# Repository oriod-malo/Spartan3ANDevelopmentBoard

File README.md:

# Spartan-3AN Development Board

## Description

A custom development board built over a Spartan-3AN FPGA. <br>
Built over 4 layers, it gives controlability over the Spartan-3AN Mode Pins through switches. This way it can be programmed both via JTAG and USB.
For the different combinations of Mode switches refer to Spartan-3AN documentation. For Slave Mode (where PIC32M250F128D acts as master), all three mode pins have to be HIGH.<br>
Note that the PIC32M250F128D requires adequate programming to function as the Master for the FPGA. 

## Features
* Spartan 3AN XC3S50AN-TQG144 FPGA
* PIC32MX250F128D-IPT for connecting with USB
* JTAG Header Pins
* M0-2 switches in order to switch from JTAG to Slave Mode to other modes and viceversa
* 4 Custom Switches
* 4 Pushbuttons
* 4 LED Lights
* VGA Connections
* All other pins connected with headers or sockets

## Images

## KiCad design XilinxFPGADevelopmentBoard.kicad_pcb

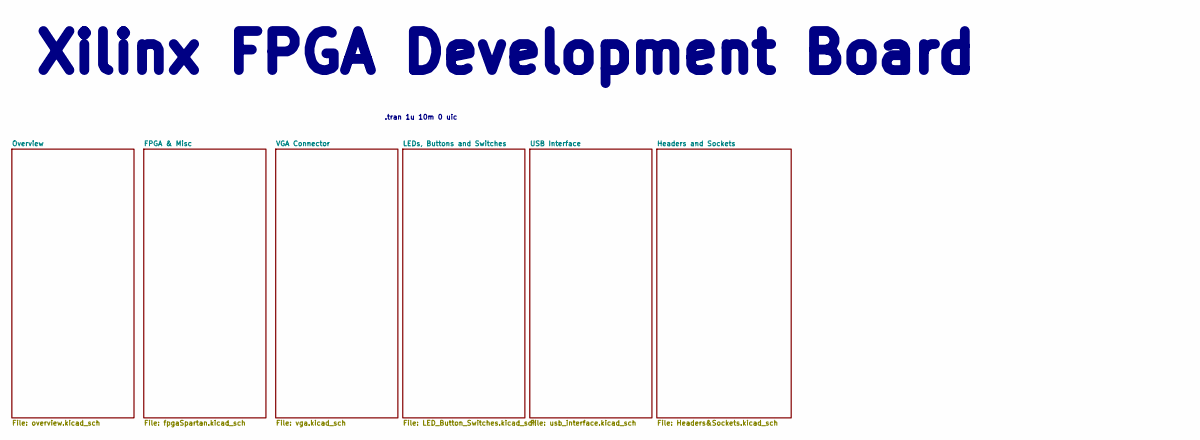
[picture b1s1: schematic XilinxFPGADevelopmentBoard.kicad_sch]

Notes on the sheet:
.tran 1u 10m 0 uic
Xilinx FPGA Development Board

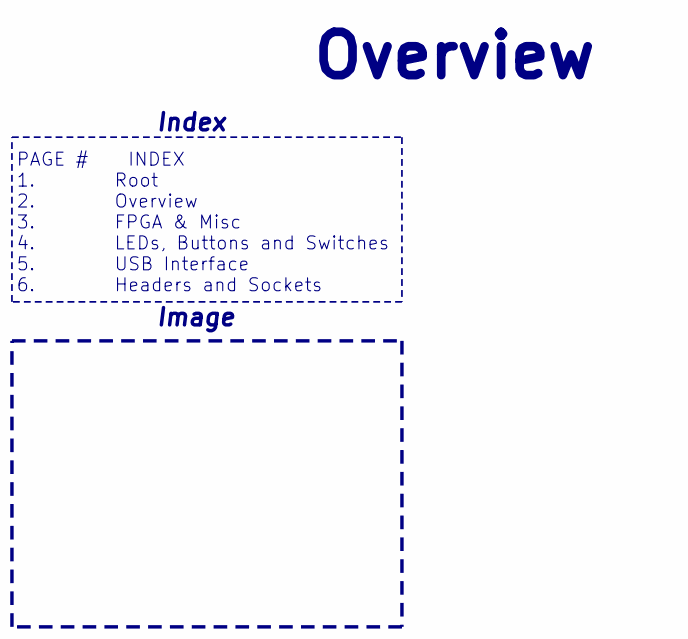
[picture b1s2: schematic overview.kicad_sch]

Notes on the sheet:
Image
Index
PAGE # INDEX 1. Root 2. Overview 3. FPGA & Misc 4. LEDs, Buttons and Switches 5. USB Interface 6. Headers and Sockets
Overview

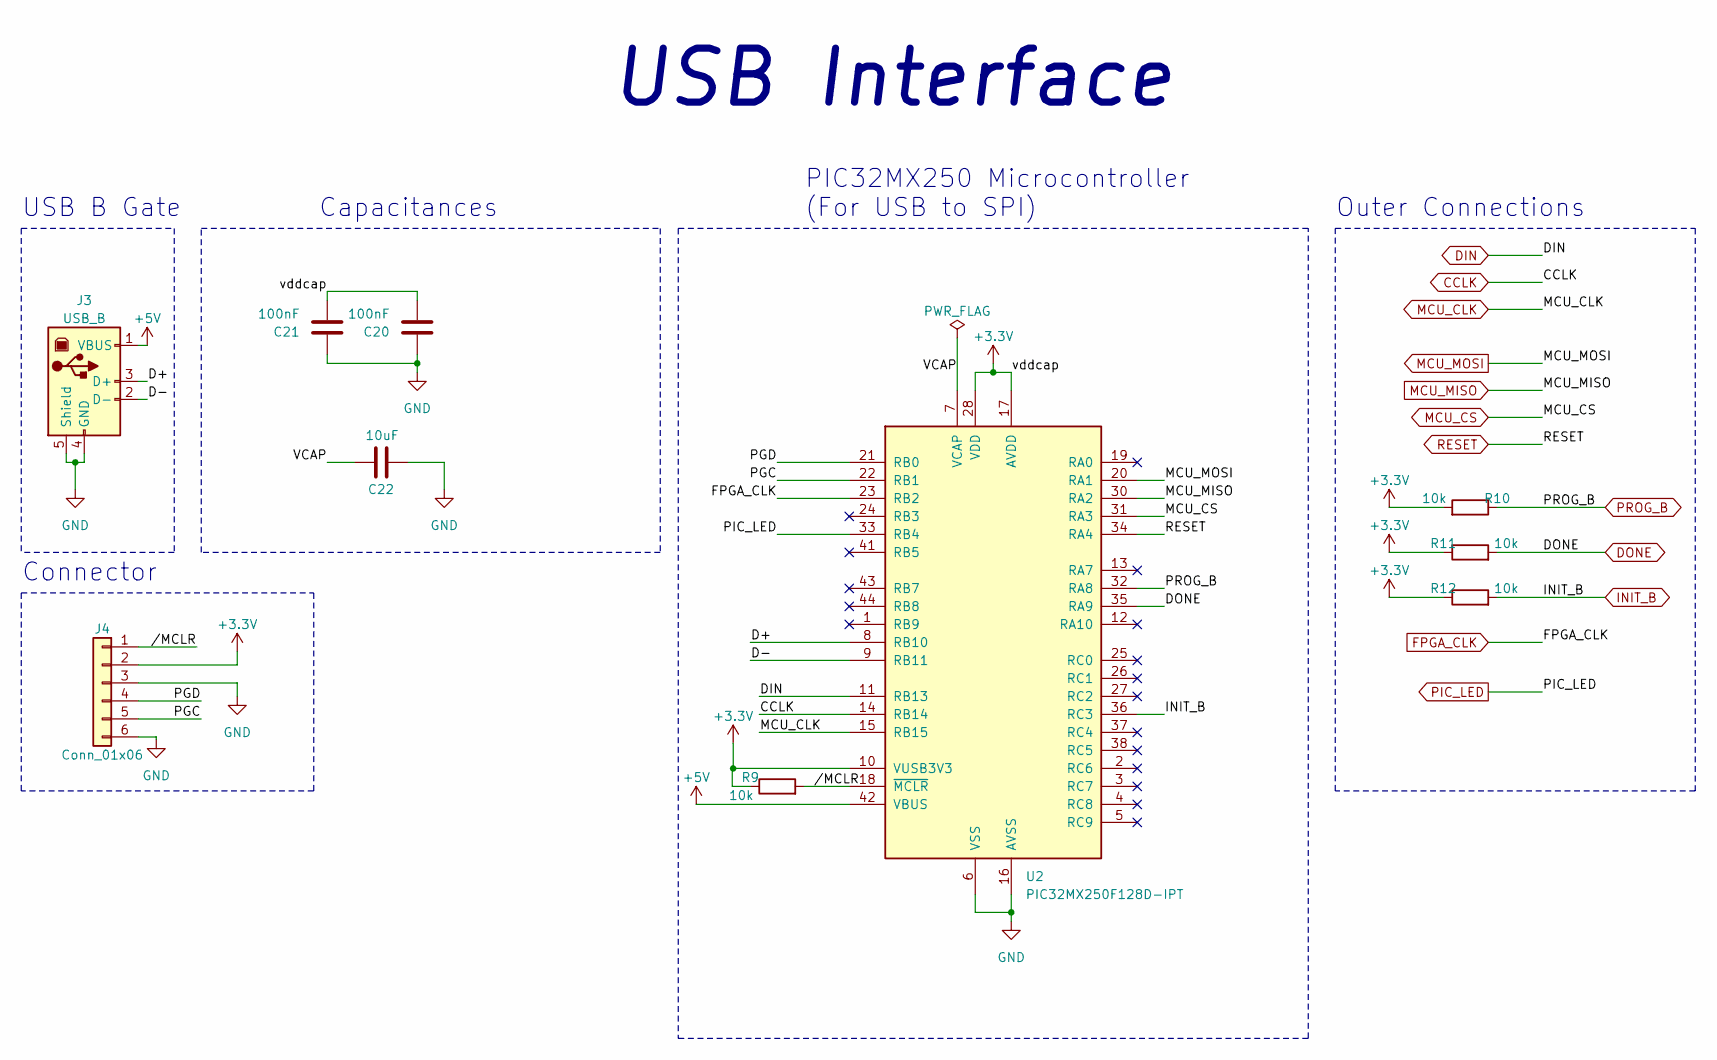
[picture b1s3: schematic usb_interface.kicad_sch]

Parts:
C20, C21: 100nF; C_0201_0603Metric
C22: 10uF; C_0201_0603Metric
J3: USB_B; USB_B_Lumberg_2411_02_Horizontal
J4: Conn_01x06; PinHeader_1x06_P2.54mm_Vertical
R9, R10, R11, R12: 10k; R_0201_0603Metric
U2: PIC32MX250F128D-IPT; TQFP-44_10x10mm_P0.8mm

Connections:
+3.3V: C20.2, C21.2, J4.2, R9.1, R10.2, R11.1, R12.1, U2.10 (VUSB3V3), U2.17 (AVDD), U2.28 (VDD), U2.40 (VDD); also elsewhere on the board
+5V: J3.1 (VBUS), U2.42 (VBUS)
/USB Interface/D+: J3.3 (D+), U2.8 (RB10)
/USB Interface/D-: J3.2 (D-), U2.9 (RB11)
/USB Interface/PGC: J4.5, U2.22 (RB1)
/USB Interface/PGD: J4.4, U2.21 (RB0)
/USB Interface/VCAP: C22.1, U2.7 (VCAP)
/USB Interface//MCLR: J4.1, R9.2, U2.18 (~MCLR)
CCLK: U2.14 (RB14); also elsewhere on the board
DIN: U2.11 (RB13); also elsewhere on the board
DONE: R11.2, U2.35 (RA9); also elsewhere on the board
FPGA_CLK: U2.23 (RB2); also elsewhere on the board
GND: C20.1, C21.1, C22.2, J3.4 (GND), J3.5 (Shield), J4.3, J4.6, U2.6 (VSS), U2.16 (AVSS), U2.29 (VSS), U2.39 (VSS); also elsewhere on the board
INIT_B: R12.2, U2.36 (RC3); also elsewhere on the board
MCU_CLK: U2.15 (RB15); also elsewhere on the board
MCU_CS: U2.31 (RA3); also elsewhere on the board
MCU_MISO: U2.30 (RA2); also elsewhere on the board
MCU_MOSI: U2.20 (RA1); also elsewhere on the board
PIC_LED: U2.33 (RB4); also elsewhere on the board
PROG_B: R10.1, U2.32 (RA8); also elsewhere on the board
RESET: U2.34 (RA4); also elsewhere on the board

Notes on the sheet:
Capacitances
USB Interface
Outer Connections
USB B Gate
PIC32MX250 Microcontroller (For USB to SPI)
Connector

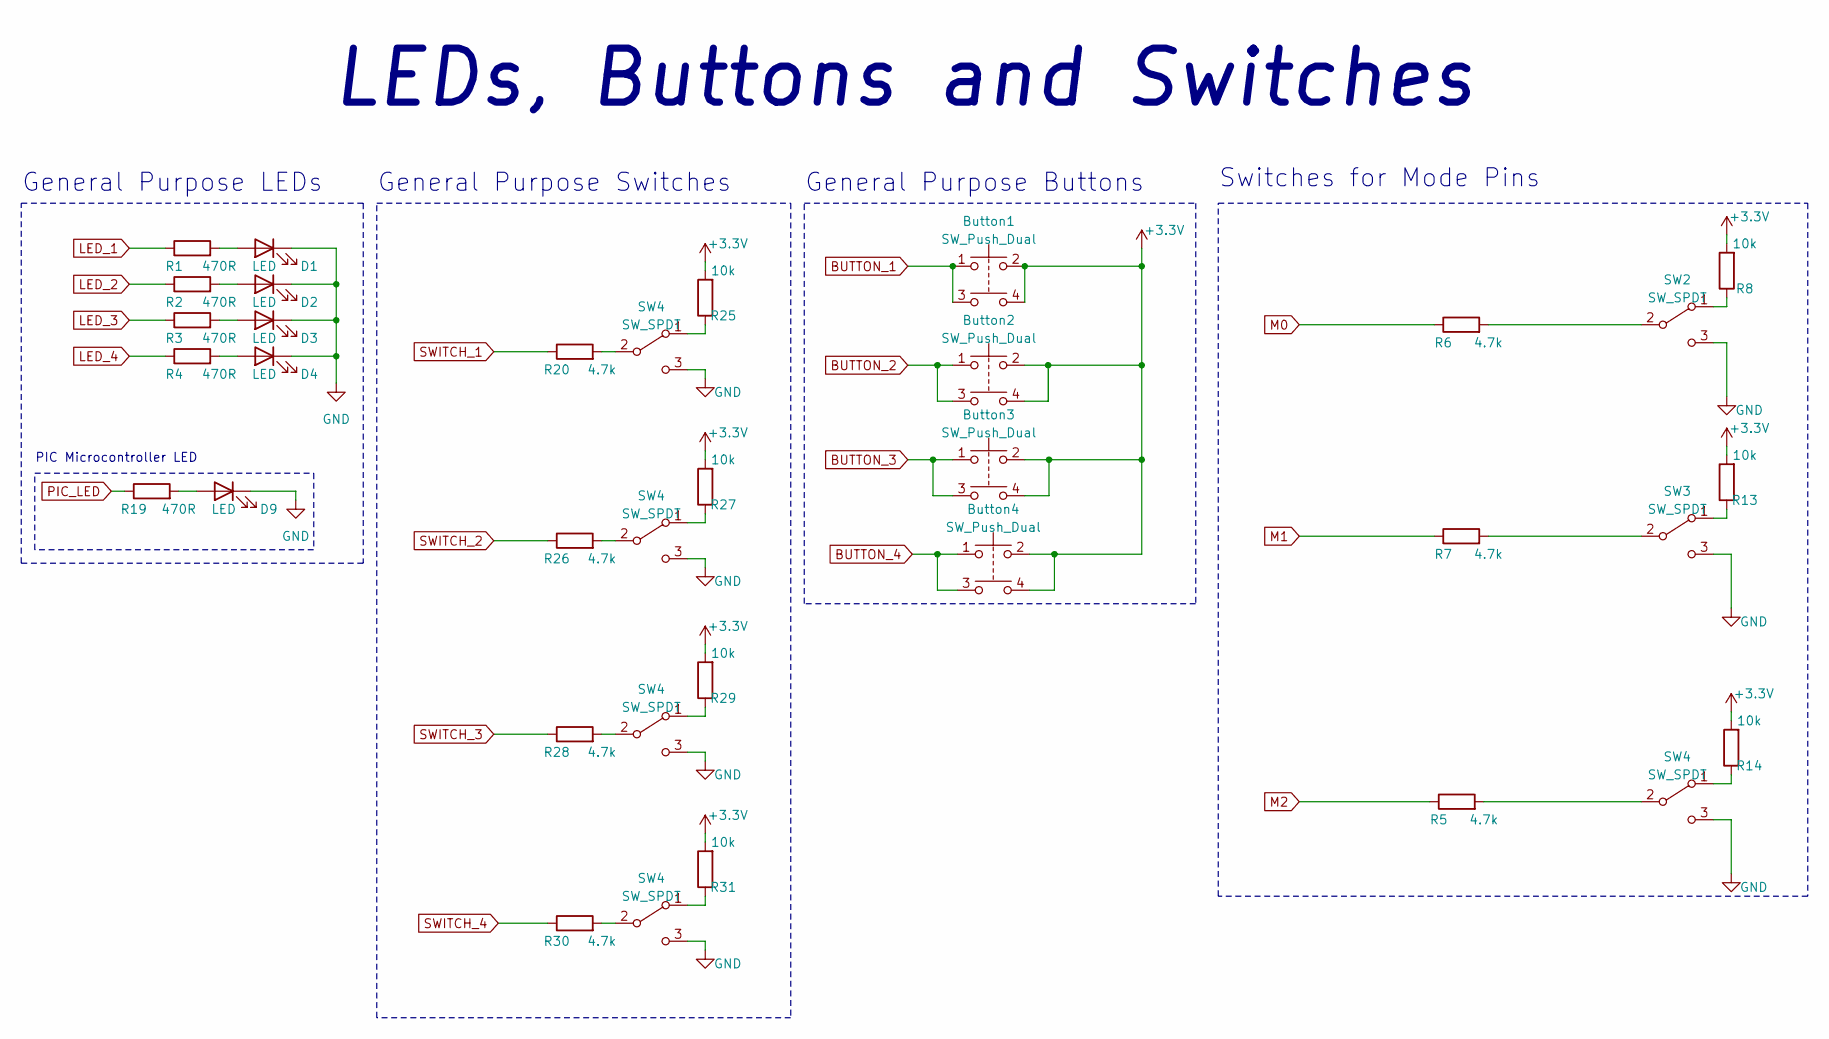
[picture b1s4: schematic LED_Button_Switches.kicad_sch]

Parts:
Button1, Button2, Button3, Button4: SW_Push_Dual; SW_PUSH_6mm
D1, D2, D3, D4: LED; LED_1206_3216Metric
D9: LED; LED_0201_0603Metric
R1, R2, R3, R4: 470R; R_1206_3216Metric
R5, R6, R7, R20, R26, R28, R30: 4.7k; R_0201_0603Metric
R8, R13, R14, R25, R27, R29, R31: 10k; R_0201_0603Metric
R19: 470R; R_0201_0603Metric
SW2, SW3, SW4: SW_SPDT; SW_500SSP1S2M2QEA

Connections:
+3.3V: Button1.2, Button1.4, Button2.2, Button2.4, Button3.2, Button3.4, Button4.2, Button4.4, R8.2, R13.2, R14.2, R25.2, R27.2, R29.2, R31.2; also elsewhere on the board
BUTTON_1: Button1.1, Button1.3; also elsewhere on the board
BUTTON_2: Button2.1, Button2.3; also elsewhere on the board
BUTTON_3: Button3.1, Button3.3; also elsewhere on the board
BUTTON_4: Button4.1, Button4.3; also elsewhere on the board
GND: D1.1 (K), D2.1 (K), D3.1 (K), D4.1 (K), D9.1 (K), SW2.3 (C), SW3.3 (C); also elsewhere on the board
LED_1: R1.1; also elsewhere on the board
LED_2: R2.1; also elsewhere on the board
LED_3: R3.1; also elsewhere on the board
LED_4: R4.1; also elsewhere on the board
M0: R6.1; also elsewhere on the board
M1: R7.1; also elsewhere on the board
M2: R5.1; also elsewhere on the board
unnamed: D1.2 (A), R1.2
unnamed: D2.2 (A), R2.2
unnamed: D3.2 (A), R3.2
unnamed: D4.2 (A), R4.2
unnamed: D9.2 (A), R19.2
unnamed 63: R25.1; also elsewhere on the board
unnamed 64: R20.2; also elsewhere on the board
unnamed 65: R27.1; also elsewhere on the board
unnamed 66: R26.2; also elsewhere on the board
unnamed 67: R29.1; also elsewhere on the board
unnamed 68: R28.2; also elsewhere on the board
unnamed 69: R31.1; also elsewhere on the board
unnamed 70: R30.2; also elsewhere on the board
PIC_LED: R19.1; also elsewhere on the board
SWITCH_1: R20.1; also elsewhere on the board
SWITCH_2: R26.1; also elsewhere on the board
SWITCH_3: R28.1; also elsewhere on the board
SWITCH_4: R30.1; also elsewhere on the board

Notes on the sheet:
General Purpose Buttons
PIC Microcontroller LED
LEDs, Buttons and Switches
General Purpose LEDs
Switches for Mode Pins
General Purpose Switches

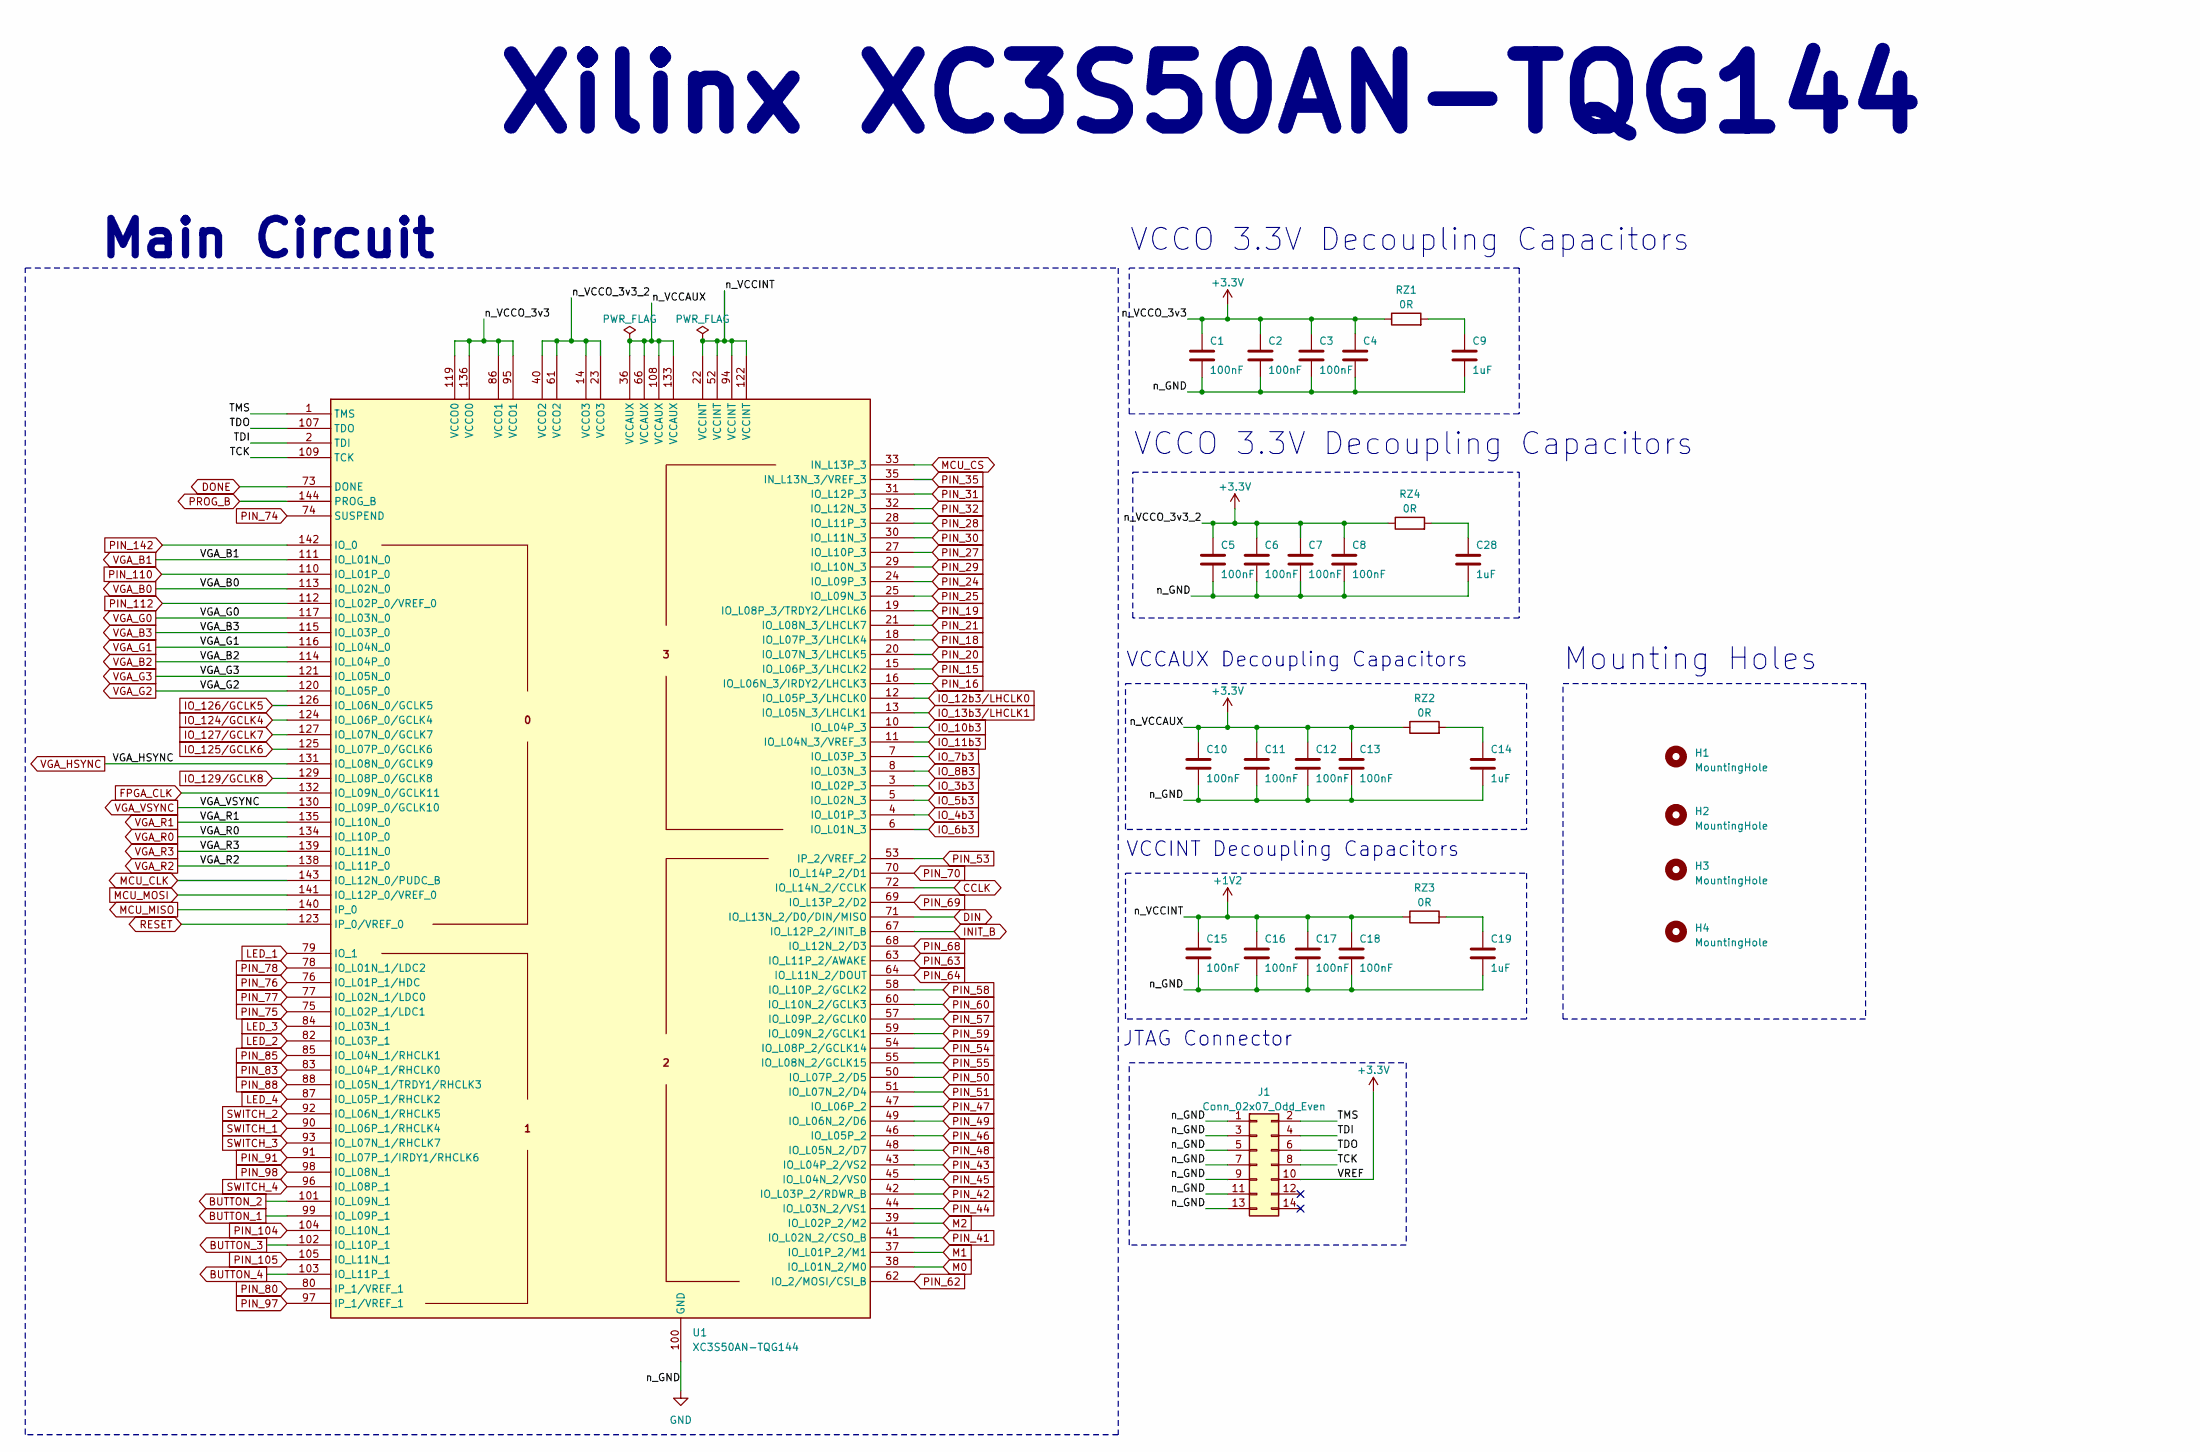
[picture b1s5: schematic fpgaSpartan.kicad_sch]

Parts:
C1, C2, C3, C4, C5, C6, C7, C8, C10, C11, C12, C13, C15, C16, C17, C18: 100nF; C_0201_0603Metric
C9, C14, C19, C28: 1uF; C_0201_0603Metric
H1, H2, H3, H4: MountingHole; MountingHole_2mm
J1: Conn_02x07_Odd_Even; IDC-Header_2x07_P2.54mm_Vertical
RZ1, RZ2, RZ3, RZ4: 0R; R_0201_0603Metric
U1: XC3S50AN-TQG144; QFP50P2200X2200X160-144N

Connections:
+1V2: C15.1, C16.1, C17.1, C18.1, RZ3.1, U1.22 (VCCINT), U1.52 (VCCINT), U1.94 (VCCINT), U1.122 (VCCINT)
+3.3V: C1.1, C2.1, C3.1, C4.1, C5.1, C6.1, C7.1, C8.1, C10.1, C11.1, C12.1, C13.1, J1.10, RZ1.1, RZ2.1, RZ4.1, U1.14 (VCCO3), U1.23 (VCCO3), U1.36 (VCCAUX), U1.40 (VCCO2), U1.61 (VCCO2), U1.66 (VCCAUX), U1.86 (VCCO1), U1.95 (VCCO1), U1.108 (VCCAUX), U1.119 (VCCO0), U1.133 (VCCAUX), U1.136 (VCCO0); also elsewhere on the board
/FPGA & Misc/TCK: J1.8, U1.109 (TCK)
/FPGA & Misc/TDI: J1.4, U1.2 (TDI)
/FPGA & Misc/TDO: J1.6, U1.107 (TDO)
/FPGA & Misc/TMS: J1.2, U1.1 (TMS)
BUTTON_1: U1.99 (IO_L09P_1); also elsewhere on the board
BUTTON_2: U1.101 (IO_L09N_1); also elsewhere on the board
BUTTON_3: U1.102 (IO_L10P_1); also elsewhere on the board
BUTTON_4: U1.103 (IO_L11P_1); also elsewhere on the board
CCLK: U1.72 (IO_L14N_2/CCLK); also elsewhere on the board
DIN: U1.71 (IO_L13N_2/D0/DIN/MISO); also elsewhere on the board
DONE: U1.73 (DONE); also elsewhere on the board
FPGA_CLK: U1.132 (IO_L09N_0/GCLK11); also elsewhere on the board
GND: C1.2, C2.2, C3.2, C4.2, C5.2, C6.2, C7.2, C8.2, C9.2, C10.2, C11.2, C12.2, C13.2, C14.2, C15.2, C16.2, C17.2, C18.2, C19.2, C28.2, J1.1, J1.3, J1.5, J1.7, J1.9, J1.11, J1.13, U1.9 (GND), U1.17 (GND), U1.26 (GND), U1.34 (GND), U1.56 (GND), U1.65 (GND), U1.81 (GND), U1.89 (GND), U1.100 (GND), U1.106 (GND), U1.118 (GND), U1.128 (GND), U1.137 (GND); also elsewhere on the board
INIT_B: U1.67 (IO_L12P_2/INIT_B); also elsewhere on the board
IO_3b3: U1.3 (IO_L02P_3); also elsewhere on the board
IO_4b3: U1.4 (IO_L01P_3); also elsewhere on the board
IO_5b3: U1.5 (IO_L02N_3); also elsewhere on the board
IO_6b3: U1.6 (IO_L01N_3); also elsewhere on the board
IO_7b3: U1.7 (IO_L03P_3); also elsewhere on the board
IO_8B3: U1.8 (IO_L03N_3); also elsewhere on the board
IO_10b3: U1.10 (IO_L04P_3); also elsewhere on the board
IO_11b3: U1.11 (IO_L04N_3/VREF_3); also elsewhere on the board
IO_12b3/LHCLK0: U1.12 (IO_L05P_3/LHCLK0); also elsewhere on the board
IO_13b3/LHCLK1: U1.13 (IO_L05N_3/LHCLK1); also elsewhere on the board
IO_124/GCLK4: U1.124 (IO_L06P_0/GCLK4); also elsewhere on the board
IO_125/GCLK6: U1.125 (IO_L07P_0/GCLK6); also elsewhere on the board
IO_126/GCLK5: U1.126 (IO_L06N_0/GCLK5); also elsewhere on the board
IO_127/GCLK7: U1.127 (IO_L07N_0/GCLK7); also elsewhere on the board
IO_129/GCLK8: U1.129 (IO_L08P_0/GCLK8); also elsewhere on the board
LED_1: U1.79 (IO_1); also elsewhere on the board
LED_2: U1.82 (IO_L03P_1); also elsewhere on the board
LED_3: U1.84 (IO_L03N_1); also elsewhere on the board
LED_4: U1.87 (IO_L05P_1/RHCLK2); also elsewhere on the board
M0: U1.38 (IO_L01N_2/M0); also elsewhere on the board
M1: U1.37 (IO_L01P_2/M1); also elsewhere on the board
M2: U1.39 (IO_L02P_2/M2); also elsewhere on the board
MCU_CLK: U1.143 (IO_L12N_0/PUDC_B); also elsewhere on the board
MCU_CS: U1.33 (IN_L13P_3); also elsewhere on the board
MCU_MISO: U1.140 (IP_0); also elsewhere on the board
MCU_MOSI: U1.141 (IO_L12P_0/VREF_0); also elsewhere on the board
unnamed: C9.1, RZ1.2
unnamed: C14.1, RZ2.2
unnamed: C19.1, RZ3.2
unnamed: C28.1, RZ4.2
PIN_15: U1.15 (IO_L06P_3/LHCLK2); also elsewhere on the board
PIN_16: U1.16 (IO_L06N_3/IRDY2/LHCLK3); also elsewhere on the board
PIN_18: U1.18 (IO_L07P_3/LHCLK4); also elsewhere on the board
PIN_19: U1.19 (IO_L08P_3/TRDY2/LHCLK6); also elsewhere on the board
PIN_20: U1.20 (IO_L07N_3/LHCLK5); also elsewhere on the board
PIN_21: U1.21 (IO_L08N_3/LHCLK7); also elsewhere on the board
PIN_24: U1.24 (IO_L09P_3); also elsewhere on the board
PIN_25: U1.25 (IO_L09N_3); also elsewhere on the board
PIN_27: U1.27 (IO_L10P_3); also elsewhere on the board
PIN_28: U1.28 (IO_L11P_3); also elsewhere on the board
PIN_29: U1.29 (IO_L10N_3); also elsewhere on the board
PIN_30: U1.30 (IO_L11N_3); also elsewhere on the board
PIN_31: U1.31 (IO_L12P_3); also elsewhere on the board
PIN_32: U1.32 (IO_L12N_3); also elsewhere on the board
PIN_35: U1.35 (IN_L13N_3/VREF_3); also elsewhere on the board
PIN_41: U1.41 (IO_L02N_2/CSO_B); also elsewhere on the board
PIN_42: U1.42 (IO_L03P_2/RDWR_B); also elsewhere on the board
PIN_43: U1.43 (IO_L04P_2/VS2); also elsewhere on the board
PIN_44: U1.44 (IO_L03N_2/VS1); also elsewhere on the board
PIN_45: U1.45 (IO_L04N_2/VS0); also elsewhere on the board
PIN_46: U1.46 (IO_L05P_2); also elsewhere on the board
PIN_47: U1.47 (IO_L06P_2); also elsewhere on the board
PIN_48: U1.48 (IO_L05N_2/D7); also elsewhere on the board
PIN_49: U1.49 (IO_L06N_2/D6); also elsewhere on the board
PIN_50: U1.50 (IO_L07P_2/D5); also elsewhere on the board
PIN_51: U1.51 (IO_L07N_2/D4); also elsewhere on the board
PIN_53: U1.53 (IP_2/VREF_2); also elsewhere on the board
PIN_54: U1.54 (IO_L08P_2/GCLK14); also elsewhere on the board
PIN_55: U1.55 (IO_L08N_2/GCLK15); also elsewhere on the board
PIN_57: U1.57 (IO_L09P_2/GCLK0); also elsewhere on the board
PIN_58: U1.58 (IO_L10P_2/GCLK2); also elsewhere on the board
PIN_59: U1.59 (IO_L09N_2/GCLK1); also elsewhere on the board
PIN_60: U1.60 (IO_L10N_2/GCLK3); also elsewhere on the board
PIN_62: U1.62 (IO_2/MOSI/CSI_B); also elsewhere on the board
PIN_63: U1.63 (IO_L11P_2/AWAKE); also elsewhere on the board
PIN_64: U1.64 (IO_L11N_2/DOUT); also elsewhere on the board
PIN_68: U1.68 (IO_L12N_2/D3); also elsewhere on the board
PIN_69: U1.69 (IO_L13P_2/D2); also elsewhere on the board
PIN_70: U1.70 (IO_L14P_2/D1); also elsewhere on the board
PIN_74: U1.74 (SUSPEND); also elsewhere on the board
PIN_75: U1.75 (IO_L02P_1/LDC1); also elsewhere on the board
PIN_76: U1.76 (IO_L01P_1/HDC); also elsewhere on the board
PIN_77: U1.77 (IO_L02N_1/LDC0); also elsewhere on the board
PIN_78: U1.78 (IO_L01N_1/LDC2); also elsewhere on the board
PIN_80: U1.80 (IP_1/VREF_1); also elsewhere on the board
PIN_83: U1.83 (IO_L04P_1/RHCLK0); also elsewhere on the board
PIN_85: U1.85 (IO_L04N_1/RHCLK1); also elsewhere on the board
PIN_88: U1.88 (IO_L05N_1/TRDY1/RHCLK3); also elsewhere on the board
PIN_91: U1.91 (IO_L07P_1/IRDY1/RHCLK6); also elsewhere on the board
PIN_97: U1.97 (IP_1/VREF_1); also elsewhere on the board
PIN_98: U1.98 (IO_L08N_1); also elsewhere on the board
PIN_104: U1.104 (IO_L10N_1); also elsewhere on the board
PIN_105: U1.105 (IO_L11N_1); also elsewhere on the board
PIN_110: U1.110 (IO_L01P_0); also elsewhere on the board
PIN_112: U1.112 (IO_L02P_0/VREF_0); also elsewhere on the board
PIN_142: U1.142 (IO_0); also elsewhere on the board
PROG_B: U1.144 (PROG_B); also elsewhere on the board
RESET: U1.123 (IP_0/VREF_0); also elsewhere on the board
SWITCH_1: U1.90 (IO_L06P_1/RHCLK4); also elsewhere on the board
SWITCH_2: U1.92 (IO_L06N_1/RHCLK5); also elsewhere on the board
SWITCH_3: U1.93 (IO_L07N_1/RHCLK7); also elsewhere on the board
SWITCH_4: U1.96 (IO_L08P_1); also elsewhere on the board
VGA_B0: U1.113 (IO_L02N_0); also elsewhere on the board
VGA_B1: U1.111 (IO_L01N_0); also elsewhere on the board
VGA_B2: U1.114 (IO_L04P_0); also elsewhere on the board
VGA_B3: U1.115 (IO_L03P_0); also elsewhere on the board
VGA_G0: U1.117 (IO_L03N_0); also elsewhere on the board
VGA_G1: U1.116 (IO_L04N_0); also elsewhere on the board
VGA_G2: U1.120 (IO_L05P_0); also elsewhere on the board
VGA_G3: U1.121 (IO_L05N_0); also elsewhere on the board
VGA_HSYNC: U1.131 (IO_L08N_0/GCLK9); also elsewhere on the board
VGA_R0: U1.134 (IO_L10P_0); also elsewhere on the board
VGA_R1: U1.135 (IO_L10N_0); also elsewhere on the board
VGA_R2: U1.138 (IO_L11P_0); also elsewhere on the board
VGA_R3: U1.139 (IO_L11N_0); also elsewhere on the board
VGA_VSYNC: U1.130 (IO_L09P_0/GCLK10); also elsewhere on the board

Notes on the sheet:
JTAG Connector
Mounting Holes
VCCAUX Decoupling Capacitors
VCCO 3.3V Decoupling Capacitors
Xilinx XC3S50AN-TQG144
VCCINT Decoupling Capacitors
Main Circuit

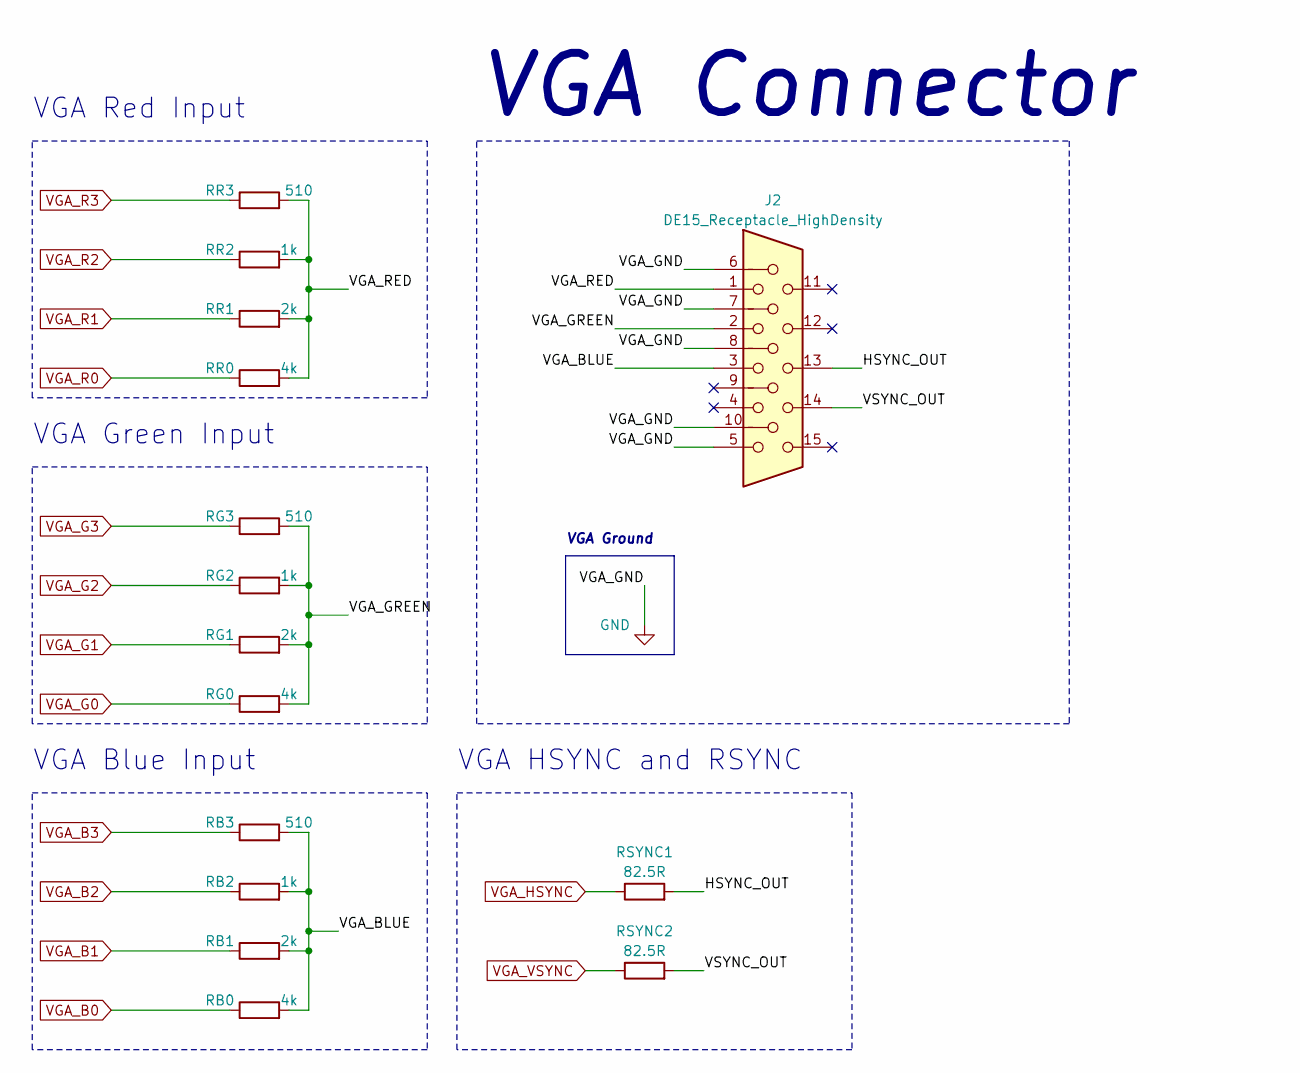
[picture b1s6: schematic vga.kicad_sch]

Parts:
J2: DE15_Receptacle_HighDensity; DSUB-15_Female_Horizontal_P2.77x2.84mm_EdgePinOffset14.56mm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
RB0: 4k; R_0201_0603Metric
RB1: 2k; R_0201_0603Metric
RB2: 1k; R_0201_0603Metric
RB3: 510; R_0201_0603Metric
RG0: 4k; R_0201_0603Metric
RG1: 2k; R_0201_0603Metric
RG2: 1k; R_0201_0603Metric
RG3: 510; R_0201_0603Metric
RR0: 4k; R_0201_0603Metric
RR1: 2k; R_0201_0603Metric
RR2: 1k; R_0201_0603Metric
RR3: 510; R_0201_0603Metric
RSYNC1, RSYNC2: 82.5R; R_0201_0603Metric

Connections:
/VGA Connector/HSYNC_OUT: J2.13, RSYNC1.2
/VGA Connector/VGA_BLUE: J2.3, RB0.2, RB1.2, RB2.2, RB3.2
/VGA Connector/VGA_GREEN: J2.2, RG0.2, RG1.2, RG2.2, RG3.2
/VGA Connector/VGA_RED: J2.1, RR0.2, RR1.2, RR2.2, RR3.2
/VGA Connector/VSYNC_OUT: J2.14, RSYNC2.2
GND: J2.5, J2.6, J2.7, J2.8, J2.10; also elsewhere on the board
VGA_B0: RB0.1; also elsewhere on the board
VGA_B1: RB1.1; also elsewhere on the board
VGA_B2: RB2.1; also elsewhere on the board
VGA_B3: RB3.1; also elsewhere on the board
VGA_G0: RG0.1; also elsewhere on the board
VGA_G1: RG1.1; also elsewhere on the board
VGA_G2: RG2.1; also elsewhere on the board
VGA_G3: RG3.1; also elsewhere on the board
VGA_HSYNC: RSYNC1.1; also elsewhere on the board
VGA_R0: RR0.1; also elsewhere on the board
VGA_R1: RR1.1; also elsewhere on the board
VGA_R2: RR2.1; also elsewhere on the board
VGA_R3: RR3.1; also elsewhere on the board
VGA_VSYNC: RSYNC2.1; also elsewhere on the board

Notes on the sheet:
VGA Green Input
VGA Blue Input
VGA Red Input
VGA Connector
VGA Ground
VGA HSYNC and RSYNC

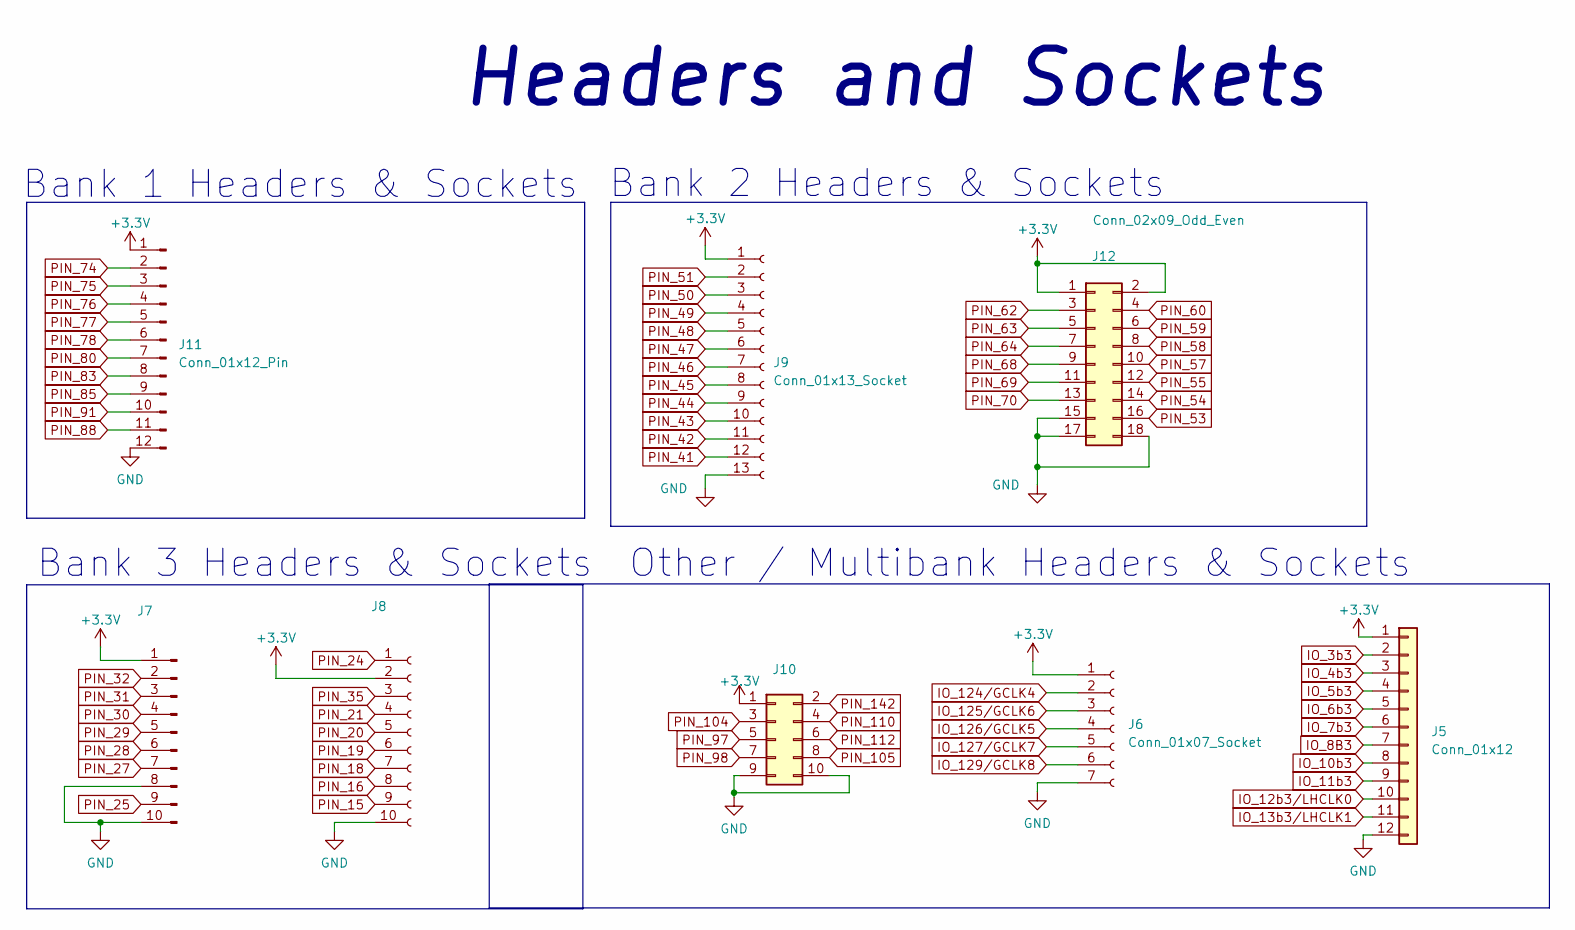
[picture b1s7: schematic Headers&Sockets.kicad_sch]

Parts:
J5: Conn_01x12; PinHeader_1x12_P2.54mm_Vertical
J6: Conn_01x07_Socket; PinSocket_1x07_P2.54mm_Vertical
J7: Conn_01x10_Pin; PinHeader_1x10_P2.54mm_Vertical
J8: Conn_01x10_Socket; PinSocket_1x10_P2.54mm_Vertical
J9: Conn_01x13_Socket; PinSocket_1x13_P2.54mm_Vertical
J10: Conn_02x05_Odd_Even; PinSocket_2x05_P2.54mm_Vertical
J11: Conn_01x12_Pin; PinHeader_1x12_P2.54mm_Vertical
J12: Conn_02x09_Odd_Even; PinSocket_2x09_P2.54mm_Vertical

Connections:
+3.3V: J5.1, J6.1, J7.1, J8.2, J9.1, J10.1, J11.1, J12.1, J12.2; also elsewhere on the board
GND: J5.12, J6.7, J7.8, J7.10, J8.10, J9.13, J10.9, J10.10, J11.12, J12.15, J12.17, J12.18; also elsewhere on the board
IO_3b3: J5.2; also elsewhere on the board
IO_4b3: J5.3; also elsewhere on the board
IO_5b3: J5.4; also elsewhere on the board
IO_6b3: J5.5; also elsewhere on the board
IO_7b3: J5.6; also elsewhere on the board
IO_8B3: J5.7; also elsewhere on the board
IO_10b3: J5.8; also elsewhere on the board
IO_11b3: J5.9; also elsewhere on the board
IO_12b3/LHCLK0: J5.10; also elsewhere on the board
IO_13b3/LHCLK1: J5.11; also elsewhere on the board
IO_124/GCLK4: J6.2; also elsewhere on the board
IO_125/GCLK6: J6.3; also elsewhere on the board
IO_126/GCLK5: J6.4; also elsewhere on the board
IO_127/GCLK7: J6.5; also elsewhere on the board
IO_129/GCLK8: J6.6; also elsewhere on the board
PIN_15: J8.9; also elsewhere on the board
PIN_16: J8.8; also elsewhere on the board
PIN_18: J8.7; also elsewhere on the board
PIN_19: J8.6; also elsewhere on the board
PIN_20: J8.5; also elsewhere on the board
PIN_21: J8.4; also elsewhere on the board
PIN_24: J8.1; also elsewhere on the board
PIN_25: J7.9; also elsewhere on the board
PIN_27: J7.7; also elsewhere on the board
PIN_28: J7.6; also elsewhere on the board
PIN_29: J7.5; also elsewhere on the board
PIN_30: J7.4; also elsewhere on the board
PIN_31: J7.3; also elsewhere on the board
PIN_32: J7.2; also elsewhere on the board
PIN_35: J8.3; also elsewhere on the board
PIN_41: J9.12; also elsewhere on the board
PIN_42: J9.11; also elsewhere on the board
PIN_43: J9.10; also elsewhere on the board
PIN_44: J9.9; also elsewhere on the board
PIN_45: J9.8; also elsewhere on the board
PIN_46: J9.7; also elsewhere on the board
PIN_47: J9.6; also elsewhere on the board
PIN_48: J9.5; also elsewhere on the board
PIN_49: J9.4; also elsewhere on the board
PIN_50: J9.3; also elsewhere on the board
PIN_51: J9.2; also elsewhere on the board
PIN_53: J12.16; also elsewhere on the board
PIN_54: J12.14; also elsewhere on the board
PIN_55: J12.12; also elsewhere on the board
PIN_57: J12.10; also elsewhere on the board
PIN_58: J12.8; also elsewhere on the board
PIN_59: J12.6; also elsewhere on the board
PIN_60: J12.4; also elsewhere on the board
PIN_62: J12.3; also elsewhere on the board
PIN_63: J12.5; also elsewhere on the board
PIN_64: J12.7; also elsewhere on the board
PIN_68: J12.9; also elsewhere on the board
PIN_69: J12.11; also elsewhere on the board
PIN_70: J12.13; also elsewhere on the board
PIN_74: J11.2; also elsewhere on the board
PIN_75: J11.3; also elsewhere on the board
PIN_76: J11.4; also elsewhere on the board
PIN_77: J11.5; also elsewhere on the board
PIN_78: J11.6; also elsewhere on the board
PIN_80: J11.7; also elsewhere on the board
PIN_83: J11.8; also elsewhere on the board
PIN_85: J11.9; also elsewhere on the board
PIN_88: J11.11; also elsewhere on the board
PIN_91: J11.10; also elsewhere on the board
PIN_97: J10.5; also elsewhere on the board
PIN_98: J10.7; also elsewhere on the board
PIN_104: J10.3; also elsewhere on the board
PIN_105: J10.8; also elsewhere on the board
PIN_110: J10.4; also elsewhere on the board
PIN_112: J10.6; also elsewhere on the board
PIN_142: J10.2; also elsewhere on the board

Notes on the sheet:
Bank 1 Headers & Sockets
Headers and Sockets
Other / Multibank Headers & Sockets
Bank 3 Headers & Sockets
Bank 2 Headers & Sockets

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
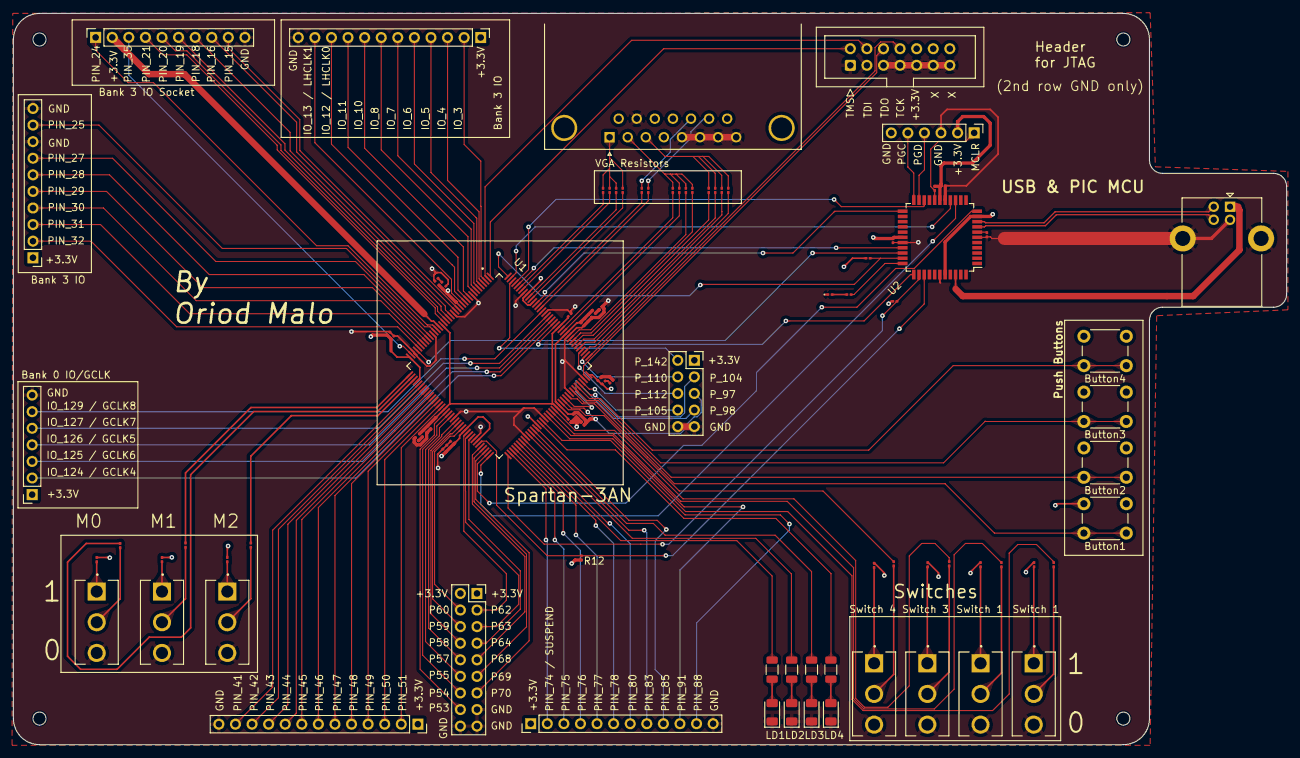
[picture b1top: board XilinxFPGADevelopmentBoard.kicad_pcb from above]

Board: 4 copper layers, 195.0 x 112.0 mm, 98 parts (0 on the bottom side), 154 nets.

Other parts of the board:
SW1, SW7, SW8, SW9, SW10: SW_SPDT; SW_500SSP1S2M2QEA

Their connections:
GND: SW1.3 (C), SW7.3 (C), SW8.3 (C), SW9.3 (C), SW10.3 (C); also elsewhere on the board
unnamed 63: SW7.1 (A); also elsewhere on the board
unnamed 64: SW7.2 (B); also elsewhere on the board
unnamed 65: SW8.1 (A); also elsewhere on the board
unnamed 66: SW8.2 (B); also elsewhere on the board
unnamed 67: SW9.1 (A); also elsewhere on the board
unnamed 68: SW9.2 (B); also elsewhere on the board
unnamed 69: SW10.1 (A); also elsewhere on the board
unnamed 70: SW10.2 (B); also elsewhere on the board
